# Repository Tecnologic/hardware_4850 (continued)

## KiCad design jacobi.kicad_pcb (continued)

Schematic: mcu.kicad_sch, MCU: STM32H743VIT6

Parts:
C601, C605, C608, C609, C610, C611, C612, C621, C622: 100n; C_0603_1608Metric; Part# CL10B104KBNC
C603, C620: 2u2; C_0603_1608Metric
C606, C607: 10u; C_1210_3225Metric; Part# CL32B106KLJNNNE
JP601: BTLDR; SolderJumper-2_P1.3mm_Open_RoundedPad1.0x1.5mm
R601: 11k; R_0603_1608Metric; Part# MCR03ERTJ113
R606, R607, R608, R609, R610, R611: 1R1; R_0603_1608Metric; Part# MCR03ERTJ1R1
R612: 10k; R_0603_1608Metric; Part# MCR03ERTJ103
U601: STM32H743VIT6; LQFP-100_14x14mm_P0.5mm; Part# 511-STM32H743VIT6; LCSC C114409
X601: Q33310F70051500; Oscillator_SMD_Abracon_ASE-4Pin_3.2x2.5mm; Part# Q33310F70051500; LCSC C32529

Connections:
+1V2: C603.1, C620.1, U601.48 (VCAP), U601.73 (VCAP)
+3.3VADC: C605.1, C606.1, C622.1, U601.20 (VREF+), U601.21 (VDDA); also elsewhere on the board
+3V3: C601.1, C607.1, C608.1, C609.1, C610.1, C611.1, C612.1, JP601.2 (B), R612.1, U601.6 (VBAT), U601.11 (VDD), U601.27 (VDD), U601.50 (VDD), U601.75 (VDD), U601.100 (VDD), X601.1 (EN), X601.4 (Vdd); also elsewhere on the board
/logic/controller/PWR_DET: R612.2, U601.3 (PE4); also elsewhere on the board
/logic/controller/PwmAH: R609.1; also elsewhere on the board
/logic/controller/PwmAL: R606.1; also elsewhere on the board
/logic/controller/PwmBH: R610.1; also elsewhere on the board
/logic/controller/PwmBL: R607.1; also elsewhere on the board
/logic/controller/PwmCH: R611.1; also elsewhere on the board
/logic/controller/PwmCL: R608.1; also elsewhere on the board
/logic/controller/analog/AIN_ACC: U601.15 (PC0); also elsewhere on the board
/logic/controller/analog/AIN_DCC: U601.32 (PC4); also elsewhere on the board
/logic/controller/analog/BrdgTemp: U601.23 (PA1); also elsewhere on the board
/logic/controller/analog/IaDC: U601.24 (PA2); also elsewhere on the board
/logic/controller/analog/IbDC: U601.25 (PA3); also elsewhere on the board
/logic/controller/analog/IcDC: U601.17 (PC2_C); also elsewhere on the board
/logic/controller/analog/MotTemp: U601.22 (PA0); also elsewhere on the board
/logic/controller/analog/V12PDC: U601.33 (PC5); also elsewhere on the board
/logic/controller/analog/VaDC: U601.35 (PB1); also elsewhere on the board
/logic/controller/analog/VbDC: U601.34 (PB0); also elsewhere on the board
/logic/controller/analog/VcDC: U601.18 (PC3_C); also elsewhere on the board
/logic/controller/interfaces/CAN_RXD: U601.81 (PD0); also elsewhere on the board
/logic/controller/interfaces/CAN_TXD: U601.82 (PD1); also elsewhere on the board
/logic/controller/interfaces/HallA: U601.59 (PD12); also elsewhere on the board
/logic/controller/interfaces/HallB: U601.60 (PD13); also elsewhere on the board
/logic/controller/interfaces/HallC: U601.61 (PD14); also elsewhere on the board
/logic/controller/interfaces/LED_ERROR: U601.98 (PE1); also elsewhere on the board
/logic/controller/interfaces/LED_MODE: U601.1 (PE2); also elsewhere on the board
/logic/controller/interfaces/LED_PWM: U601.2 (PE3); also elsewhere on the board
/logic/controller/interfaces/LED_RUN: U601.97 (PE0); also elsewhere on the board
/logic/controller/interfaces/PWM_EN: U601.45 (PE15); also elsewhere on the board
/logic/controller/interfaces/SWCLK: U601.76 (PA14); also elsewhere on the board
/logic/controller/interfaces/SWDIO: U601.72 (PA13); also elsewhere on the board
/logic/controller/interfaces/SWO: U601.89 (PB3); also elsewhere on the board
/logic/controller/mcu/AIN_VDC: U601.16 (PC1), U601.36 (PB2); also elsewhere on the board
/logic/controller/mcu/USB_DM: U601.70 (PA11); also elsewhere on the board
/logic/controller/mcu/USB_DP: U601.71 (PA12); also elsewhere on the board
/logic/controller/mcu/USB_VBUS: U601.4 (PE5); also elsewhere on the board
/logic/controller/mcu/\RESET: C621.1, U601.14 (NRST); also elsewhere on the board
GNDA: C605.2, C606.2, C622.2, U601.19 (VSSA); also elsewhere on the board
GNDD: C601.2, C603.2, C607.2, C608.2, C609.2, C610.2, C611.2, C612.2, C620.2, C621.2, R601.1, U601.10 (VSS), U601.26 (VSS), U601.49 (VSS), U601.74 (VSS), U601.99 (VSS), X601.2 (GND); also elsewhere on the board
unnamed: JP601.1 (A), R601.2, U601.94 (BOOT0)
unnamed: R609.2, U601.67 (PA8)
unnamed: R610.2, U601.68 (PA9)
unnamed: R611.2, U601.69 (PA10)
unnamed: R606.2, U601.52 (PB13)
unnamed: R607.2, U601.53 (PB14)
unnamed: R608.2, U601.54 (PB15)
unnamed: U601.12 (PH0), X601.3 (OUT)

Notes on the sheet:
STM32H743VIT6 core: supply decoupling, reset/boot/clock, PWM gate-drive series resistors

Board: 4 copper layers, 248 parts (15 on the bottom side), 157 nets, no tracks yet.

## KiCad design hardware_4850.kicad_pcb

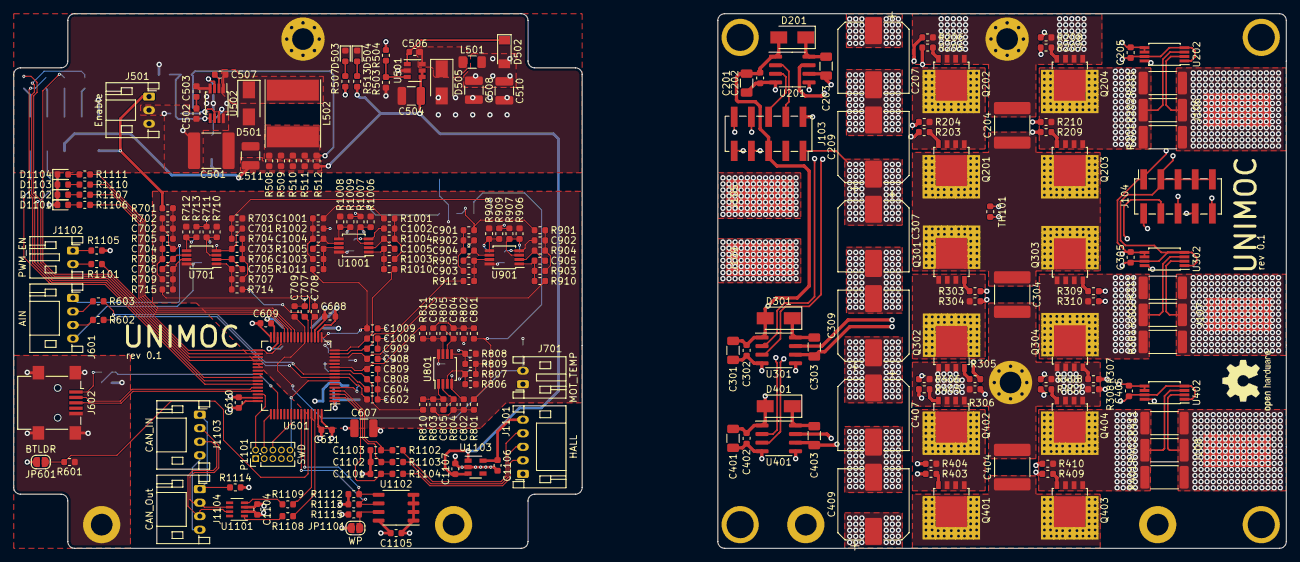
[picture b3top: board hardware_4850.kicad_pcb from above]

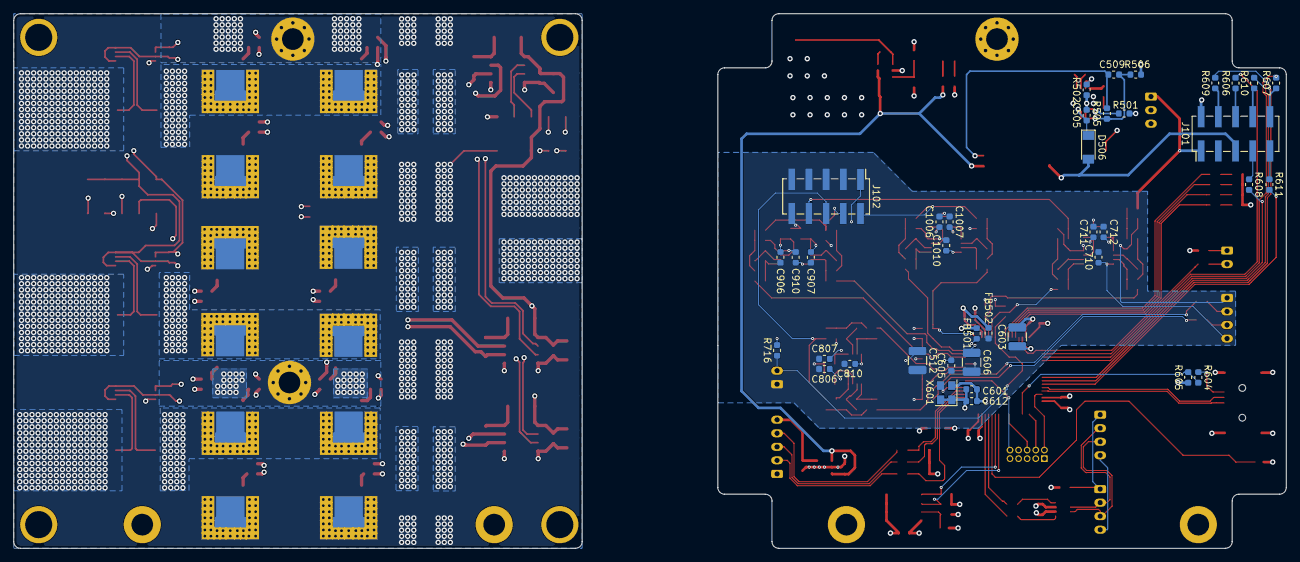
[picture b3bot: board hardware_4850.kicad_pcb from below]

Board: 4 copper layers, 188.1 x 79.0 mm, 290 parts (39 on the bottom side), 171 nets.

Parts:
C201, C203, C301, C303, C401, C403: 10u; C_1206_3216Metric
C202, C205, C302, C305, C402, C405, C502, C503, C506, C507, C601, C602, C604, C605, C608, C609, C610, C611, C612, C701, C707, C708, C709, C710, C711, C712, C806, C807, C808, C810, C906, C907, C908, C910, C1006, C1007, C1008, C1010, C1101, C1102, C1103, C1104, C1105: 100n; C_0603_1608Metric
C204, C304, C404, C501: 10u; C_2220_5650Metric
C207, C209, C307, C309, C407, C409: 56u; CP_Elec_10x10
C504, C508, C510, C511, C512: 22u; C_1210_3225Metric
C505, C1106, C1107: 1u; C_0603_1608Metric
C509: 2n2; C_0603_1608Metric
C603, C606, C607: 10u; C_1210_3225Metric
C702, C705, C706: 1n; C_0603_1608Metric
C703, C704: 10n; C_0603_1608Metric
C801, C802, C804, C901, C902, C904, C1001, C1002, C1004: 4n7; C_0603_1608Metric
C803, C805, C903, C905, C1003, C1005: 47p; C_0603_1608Metric
C809, C909, C1009: 100p; C_0603_1608Metric
D201, D301, D401, D501, D505: SS110R3G; D_SMA
D502, D506: PMLL4153; D_MiniMELF
D503: 3V3; LED_0603_1608Metric
D504: 12V; LED_0603_1608Metric
D1101: RUN; LED_0603_1608Metric
D1102: ERROR; LED_0603_1608Metric
D1103: FW; LED_0603_1608Metric
D1104: PWM; LED_0603_1608Metric
FB501, FB502: Ferrite_Bead_Small; R_0603_1608Metric
H101, H105, H106: GND; MountingHole_3.2mm_M3_Pad_Via
H102, H103, H104, H107: GND; MountingHole_3.2mm_M3_ISO14580_Pad
J101: PWM; PinHeader_2x05_P2.54mm_Vertical_SMD
J102: ADC; PinHeader_2x05_P2.54mm_Vertical_SMD
J103: PWM; PinSocket_2x05_P2.54mm_Vertical_SMD
J104: ADC; PinSocket_2x05_P2.54mm_Vertical_SMD
J105: +; SolderWirePad_1x01_SMD_5x10mm
J106: A; SolderWirePad_1x01_SMD_5x10mm
J107: B; SolderWirePad_1x01_SMD_5x10mm
J108: C; SolderWirePad_1x01_SMD_5x10mm
J109: GND; SolderWirePad_1x01_SMD_5x10mm
J501: Enable; JST_PH_S3B-PH-K_1x03_P2.00mm_Horizontal
J601: AIN; JST_PH_S4B-PH-K_1x04_P2.00mm_Horizontal
J602: USB_B_Mini; USB_Mini-B_Lumberg_2486_01_Horizontal
J701: MOT_TEMP; JST_PH_S2B-PH-K_1x02_P2.00mm_Horizontal
J1101: HALL; JST_PH_S5B-PH-K_1x05_P2.00mm_Horizontal
J1102: PWM_EN; JST_PH_S2B-PH-K_1x02_P2.00mm_Horizontal
J1103: CAN_IN; JST_PH_S4B-PH-K_1x04_P2.00mm_Horizontal
J1104: CAN_Out; JST_PH_S4B-PH-K_1x04_P2.00mm_Horizontal
JP601: BTLDR; SolderJumper-2_P1.3mm_Open_RoundedPad1.0x1.5mm
JP1101: WP; SolderJumper-2_P1.3mm_Open_RoundedPad1.0x1.5mm
L501: 4u7; L_1206_3216Metric
L502: 330u; L_Taiyo-Yuden_NR-80xx_HandSoldering
N101: Housing_Pad; RND-455-00370
P1101: SWD; PinHeader_2x05_P1.27mm_Vertical
Q201, Q202, Q203, Q204, Q301, Q302, Q303, Q304, Q401, Q402, Q403, Q404: NCEP6080AG; LFPAK56_ThermalVias-1
R201, R202, R211, R301, R302, R311, R401, R402, R411: 2mR; R_2512_6332Metric
R203, R204, R205, R206, R207, R208, R209, R210, R303, R304, R305, R306, R307, R308, R309, R310, R403, R404, R405, R406, R407, R408, R409, R410, R606, R607, R608, R609, R610, R611: 1R1; R_0603_1608Metric
R501: 220k; R_0603_1608Metric
R502: 100k; R_0603_1608Metric
R503, R505, R601, R602, R603, R605, R710, R711, R712, R713, R806, R807, R808, R809, R906, R907, R908, R909, R1006, R1007, R1008, R1009, R1115: 11k; R_0603_1608Metric
R504: 34k; R_0603_1608Metric
R506: 2k7; R_0603_1608Metric
R507, R1101, R1102, R1103, R1104, R1105, R1106, R1107, R1110, R1111: 510R; R_0603_1608Metric
R508, R509, R510, R511, R512, R1108, R1109, R1114: 11R; R_0603_1608Metric
R513: 3k3; R_0603_1608Metric
R604, R704, R705, R707, R709, R802, R902, R1002, R1112, R1113: 4k7; R_0603_1608Metric
R701: 24k 0.1%; R_0603_1608Metric
R702: 1k2 0.1%; R_0603_1608Metric
R703, R716: 10k 0.1%; R_0603_1608Metric
R706, R708: 47k; R_0603_1608Metric
R714, R715, R810, R811, R910, R911, R1010, R1011: 21R; R_0603_1608Metric
R801, R803, R901, R903, R1001, R1003: 9k1; R_0603_1608Metric
R804, R904, R1004: 470k; R_0603_1608Metric
R805, R905, R1005: 910k; R_0603_1608Metric
TH101: NTC 10k; R_0603_1608Metric
U201, U301, U401: LM5109BMA; SOIC-8_3.9x4.9mm_P1.27mm
U202, U302, U402: INA240A1PWR; TSSOP-8_4.4x3mm_P0.65mm
U501: LMR12010Y; SOT-23-6
U502: LM5008; MSOP-8_3x3mm_P0.65mm
U601: STM32F730R8Tx; LQFP-64_10x10mm_P0.5mm
U701, U801, U901, U1001: GS8632-MR; MSOP-8_3x3mm_P0.65mm
U1101: TCAN334; SOT-23-8
U1102: 24LC04; SO-8_3.9x4.9mm_P1.27mm
U1103: AP2204K-5.0; SOT-23-5
X601: SM44T; Oscillator_SMD_Abracon_ASE-4Pin_3.2x2.5mm

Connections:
+1V2: C603.1, U601.30
+3.3VA: C205.1, C305.1, C405.1, J104.1, U202.5, U202.6, U302.5, U302.6, U402.5, U402.6
+3.3VADC: C512.1, C605.1, C606.1, C710.1, C810.1, C910.1, C1010.1, FB501.1, J102.1, J601.4, R703.2, R710.2, R712.2, R716.2, R806.1, R808.1, R906.1, R908.1, R1006.1, R1008.1, U601.13, U701.8, U801.8, U901.8, U1001.8
+3V3: C508.1, C510.1, C601.1, C607.1, C608.1, C609.1, C610.1, C611.1, C612.1, C1104.1, C1105.1, D502.2, FB501.2, JP601.2, JP1101.1, L501.2, P1101.1, R504.2, R507.2, R1105.2, R1112.1, R1113.1, U601.1, U601.19, U601.32, U601.48, U601.64, U1101.3, U1102.8, X601.1, X601.4
+12P: C201.1, C202.1, C301.1, C302.1, C401.1, C402.1, D201.2, D301.2, D401.2, J103.5, U201.1, U301.1, U401.1
+12V: C504.1, C511.1, C1107.1, D506.2, J101.5, R508.1, R509.1, R510.1, R511.1, R512.1, R513.1, U501.4, U501.5, U1103.1, U1103.3
+48V: J101.1, J501.1, R701.2
+BATT: C204.1, C207.1, C209.1, C304.1, C307.1, C309.1, C404.1, C407.1, C409.1, J103.1, J105.1, Q201.5, Q203.5, Q301.5, Q303.5, Q401.5, Q403.5
/logic/controller/AIN_ACC: C602.1, R602.2, U601.8
/logic/controller/AIN_CUR_A: C808.2, R810.1, U601.10
/logic/controller/AIN_CUR_A_AC: C809.2, R811.1, U601.11
/logic/controller/AIN_DCC: C604.1, R603.2, U601.9
/logic/controller/BTLDR: JP601.1, R601.2, U601.60
/logic/controller/CAN_RX: R1109.2, U601.61
/logic/controller/CAN_TX: R1108.2, U601.62
/logic/controller/CLK: U601.5, X601.3
/logic/controller/EEPROM_SCL: R1113.2, U601.58, U1102.6
/logic/controller/EEPROM_SDA: R1112.2, U601.59, U1102.5
/logic/controller/Ia: C801.2, J102.6, R801.2
/logic/controller/Ib: C901.2, J102.4, R901.2
/logic/controller/Ic: C1001.2, J102.2, R1001.2
/logic/controller/PwmAH: J101.4, R609.1
/logic/controller/PwmAL: J101.6, R606.1
/logic/controller/PwmBH: J101.8, R610.1
/logic/controller/PwmBL: J101.10, R607.1
/logic/controller/PwmCH: J101.9, R611.1
/logic/controller/PwmCL: J101.7, R608.1
/logic/controller/TCK-SWCLK: P1101.4, U601.49
/logic/controller/TDO-SWO: P1101.6, U601.55
/logic/controller/TMS-SWDIO: P1101.2, U601.46
/logic/controller/Temp+: C701.1, J102.8, R703.1, R704.2
/logic/controller/USB_DM: J602.2, U601.44
/logic/controller/USB_DP: J602.3, U601.45
/logic/controller/USB_VBUS: R604.2, R605.2, U601.51
/logic/controller/\RESET: P1101.10, U601.7
/logic/controller/analog/BrdgTemp: C707.1, R714.2, U601.21
/logic/controller/analog/IbAC: C909.2, R911.1, U601.15
/logic/controller/analog/IbDC: C908.2, R910.1, U601.14
/logic/controller/analog/IcAC: C1009.2, R1011.1, U601.17
/logic/controller/analog/IcDC: C1008.2, R1010.1, U601.16
/logic/controller/analog/MotTemp: C709.1, J701.2, R716.1, U601.22
/logic/controller/analog/Vdc: C708.1, R715.2, U601.20
/logic/controller/interfaces/HallA: C1101.1, R1104.1, U601.2
/logic/controller/interfaces/HallB: C1102.1, R1103.1, U601.3
/logic/controller/interfaces/HallC: C1103.1, R1102.1, U601.4
/logic/controller/interfaces/LED_ERROR: R1107.2, U601.27
/logic/controller/interfaces/LED_MODE: R1110.2, U601.26
/logic/controller/interfaces/LED_PWM: R1111.2, U601.25
/logic/controller/interfaces/LED_RUN: R1106.2, U601.28
/logic/controller/interfaces/PWM_EN: R1101.2, U601.29, U601.33
/power/phase_a/I: J104.6, U202.8
/power/phase_a/Phase: J106.1, R201.1, R202.1, R211.1, U202.2
/power/phase_a/PwmH: J103.4, U201.2
/power/phase_a/PwmL: J103.6, U201.3
/power/phase_b/I: J104.4, U302.8
/power/phase_b/Phase: J107.1, R301.1, R302.1, R311.1, U302.2
/power/phase_b/PwmH: J103.8, U301.2
/power/phase_b/PwmL: J103.10, U301.3
/power/phase_c/I: J104.2, U402.8
/power/phase_c/Phase: J108.1, R401.1, R402.1, R411.1, U402.2
/power/phase_c/PwmH: J103.9, U401.2
/power/phase_c/PwmL: J103.7, U401.3
GND: C205.2, C305.2, C405.2, J104.3, J104.5, J104.7, J104.9, U202.1, U202.4, U202.7, U302.1, U302.4, U302.7, U402.1, U402.4, U402.7
GNDA: C512.2, C602.2, C604.2, C605.2, C606.2, C701.2, C702.1, C703.1, C704.1, C707.2, C708.2, C709.2, C710.2, C711.2, C712.2, C802.1, C806.1, C807.1, C808.1, C809.1, C810.2, C902.1, C906.1, C907.1, C908.1, C909.1, C910.2, C1002.1, C1006.1, C1007.1, C1008.1, C1009.1, C1010.2, FB502.1, J102.3, J102.5, J102.7, J102.9, J102.10, J601.1, J701.1, R702.2, R711.1, R713.1, R802.2, R807.2, R809.2, R902.2, R907.2, R909.2, R1002.2, R1007.2, R1009.2, U601.12, U701.4, U801.4, U901.4, U1001.4
GNDD: C501.2, C503.2, C504.2, C505.1, C508.2, C510.2, C511.2, C601.2, C603.2, C607.2, C608.2, C609.2, C610.2, C611.2, C612.2, C1101.2, C1102.2, C1103.2, C1104.2, C1105.2, C1106.2, C1107.2, D501.2, D503.1, D504.1, D505.2, D1101.1, D1102.1, D1103.1, D1104.1, FB502.2, H101.1, H102.1, H103.1, J101.2, J501.3, J602.5, J602.6, J1101.1, P1101.3, P1101.5, R502.1, R503.1, R506.1, R601.1, R605.1, R1114.2, R1115.2, U501.2, U502.4, U601.18, U601.31, U601.47, U601.63, U1101.2, U1102.1, U1102.2, U1102.3, U1102.4, U1103.2, X601.2
GNDPWR: C204.2, C207.2, C209.2, C304.2, C307.2, C309.2, C404.2, C407.2, C409.2, H104.1, H105.1, H106.1, H107.1, J103.2, J109.1, N101.1, Q202.1, Q202.2, Q202.3, Q204.1, Q204.2, Q204.3, Q302.1, Q302.2, Q302.3, Q304.1, Q304.2, Q304.3, Q402.1, Q402.2, Q402.3, Q404.1, Q404.2, Q404.3, R206.1, R208.1, R306.1, R308.1, R406.1, R408.1
unnamed: C502.2, C503.1
unnamed: C509.1, L502.2, R505.2, R508.2, R509.2, R510.2, R511.2, R512.2
unnamed: C702.2, R701.1, R702.1, R705.2
unnamed: C703.2, R704.1, R706.2, R707.2
unnamed: C704.2, R705.1, R708.2, R709.2
unnamed: C801.1, C803.2, C804.2, R802.1
unnamed: C802.2, R801.1, R803.2, R804.2
unnamed: C901.1, C903.2, C904.2, R902.1
unnamed: C902.2, R901.1, R903.2, R904.2
unnamed: C1001.1, C1003.2, C1004.2, R1002.1
unnamed: C1002.2, R1001.1, R1003.2, R1004.2
unnamed: C203.1, D201.1, U201.8
unnamed: C303.1, D301.1, U301.8
unnamed: C403.1, D401.1, U401.8
unnamed: C507.1, D501.1, L502.1, U502.1
unnamed: C506.2, D502.1, U501.1
unnamed: D503.2, R507.1
unnamed: D504.2, R513.2
unnamed: C506.1, D505.1, L501.1, U501.6
unnamed: C505.2, D506.1, U502.7
unnamed: D1101.2, R1106.1
unnamed: D1102.2, R1107.1
unnamed: D1103.2, R1110.1
unnamed: D1104.2, R1111.1
unnamed: J104.8, TH101.1
unnamed: J104.10, TH101.2
unnamed: C501.1, C502.1, J501.2, R501.2, U502.8
unnamed: J601.2, R603.1
unnamed: J601.3, R602.1
unnamed: J602.1, R604.1
unnamed: J1101.2, R1104.2
unnamed: J1101.3, R1103.2
unnamed: J1101.4, R1102.2
unnamed: C1106.1, J1101.5, U1103.5
unnamed: J1102.1, R1105.1
unnamed: J1102.2, R1101.1
unnamed: J1103.1, J1104.1, R1114.1
unnamed: J1103.2, J1104.2, U1101.6
unnamed: J1103.3, J1104.3, U1101.7
unnamed: J1103.4, J1104.4
unnamed: JP1101.2, R1115.1, U1102.7
unnamed: Q201.4, R203.1
unnamed: Q201.1, Q201.2, Q201.3, Q202.5, Q203.1, Q203.2, Q203.3, Q204.5, R201.2, R202.2, R204.1, R210.1, R211.2, U202.3
unnamed: Q202.4, R205.1
unnamed: Q203.4, R209.1
unnamed: Q204.4, R207.1
unnamed: Q301.4, R303.1
unnamed: Q301.1, Q301.2, Q301.3, Q302.5, Q303.1, Q303.2, Q303.3, Q304.5, R301.2, R302.2, R304.1, R310.1, R311.2, U302.3
unnamed: Q302.4, R305.1
unnamed: Q303.4, R309.1
unnamed: Q304.4, R307.1
unnamed: Q401.4, R403.1
unnamed: Q401.1, Q401.2, Q401.3, Q402.5, Q403.1, Q403.2, Q403.3, Q404.5, R401.2, R402.2, R404.1, R410.1, R411.2, U402.3
unnamed: Q402.4, R405.1
unnamed: Q403.4, R409.1
unnamed: Q404.4, R407.1
unnamed: R203.2, R209.2, U201.7
unnamed: C203.2, R204.2, R210.2, U201.6
unnamed: R205.2, R207.2, U201.5
unnamed: C201.2, C202.2, R206.2, R208.2, U201.4
unnamed: R303.2, R309.2, U301.7
unnamed: C303.2, R304.2, R310.2, U301.6
unnamed: R305.2, R307.2, U301.5
unnamed: C301.2, C302.2, R306.2, R308.2, U301.4
unnamed: R403.2, R409.2, U401.7
unnamed: C403.2, R404.2, R410.2, U401.6
unnamed: R405.2, R407.2, U401.5
unnamed: C401.2, C402.2, R406.2, R408.2, U401.4
unnamed: R503.2, R504.1, U501.3
unnamed: C507.2, U502.2
unnamed: C509.2, R505.1, R506.2, U502.5
unnamed: R502.2, U502.3
unnamed: R501.1, U502.6
unnamed: R609.2, U601.41
unnamed: R610.2, U601.42
unnamed: R611.2, U601.43
unnamed: R606.2, U601.34
unnamed: R607.2, U601.35
unnamed: R608.2, U601.36
unnamed: C711.1, R710.1, R711.2, U701.3
unnamed: C705.2, R706.1, U701.2
unnamed: C705.1, R707.1, R714.1, U701.1
unnamed: C712.1, R712.1, R713.2, U701.5
unnamed: C706.2, R708.1, U701.6
unnamed: C706.1, R709.1, R715.1, U701.7
unnamed: C806.2, R806.2, R807.1, U801.3
unnamed: C805.1, R804.1, U801.2
unnamed: C805.2, R803.1, R810.2, U801.1
unnamed: C807.2, R808.2, R809.1, U801.5
unnamed: C804.1, R805.2, U801.6
unnamed: C803.1, R805.1, R811.2, U801.7
unnamed: C906.2, R906.2, R907.1, U901.3
unnamed: C905.1, R904.1, U901.2
unnamed: C905.2, R903.1, R910.2, U901.1
unnamed: C907.2, R908.2, R909.1, U901.5
unnamed: C904.1, R905.2, U901.6
unnamed: C903.1, R905.1, R911.2, U901.7
unnamed: C1006.2, R1006.2, R1007.1, U1001.3
unnamed: C1005.1, R1004.1, U1001.2
unnamed: C1005.2, R1003.1, R1010.2, U1001.1
unnamed: C1007.2, R1008.2, R1009.1, U1001.5
unnamed: C1004.1, R1005.2, U1001.6
unnamed: C1003.1, R1005.1, R1011.2, U1001.7
unnamed: R1109.1, U1101.4
unnamed: R1108.1, U1101.1

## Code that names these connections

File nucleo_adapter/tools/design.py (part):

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], [
    dict(ref='J101', lib='Connector_Generic:Conn_02x05_Odd_Even', value='PWM',
         fp='Connector_PinHeader_2.54mm:PinHeader_2x05_P2.54mm_Vertical_SMD',
         pins={'1': '+BATT', '2': 'GND', '3': NC, '4': 'PWM_AH', '5': '+12V',
               '6': 'PWM_AL', '7': 'PWM_CL', '8': 'PWM_BH', '9': 'PWM_CH', '10': 'PWM_BL'}),
    dict(ref='J102', lib='Connector_Generic:Conn_02x05_Odd_Even', value='ADC',
         fp='Connector_PinHeader_2.54mm:PinHeader_2x05_P2.54mm_Vertical_SMD',
         pins={'1': '+3.3VA', '2': 'I_C', '3': 'GNDA', '4': 'I_B', '5': 'GNDA',
               '6': 'I_A', '7': 'GNDA', '8': 'T_BRIDGE', '9': 'GNDA', '10': 'GNDA'}),
    dict(ref='H101', lib='Mechanical:MountingHole_Pad', value='M3',
         fp='MountingHole:MountingHole_3.2mm_M3_Pad_Via', pins={'1': 'GND'}),
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
# ---------------------------------------------------------------- nucleo
NUCLEO_MAP = {
    'PE9': 'TIM1_CH1', 'PE8': 'TIM1_CH1N', 'PE11': 'TIM1_CH2', 'PE10': 'TIM1_CH2N',
    'PE13': 'TIM1_CH3', 'PE12': 'TIM1_CH3N', 'PE15': 'TIM1_BKIN',
    'PA6': 'ADC_IA', 'PB1': 'ADC_IB', 'PC2': 'ADC_IC', 'PC3': 'ADC_VDC',
    'PF11': 'ADC_VA', 'PF13': 'ADC_VB', 'PF10': 'ADC_VC',
    'PF12': 'ADC_TBRIDGE', 'PF14': 'ADC_TMOTOR',
    'PD12': 'HALL_A', 'PD13': 'HALL_B', 'PD14': 'HALL_C',
    'PD0': 'CAN_RX', 'PD1': 'CAN_TX',
    '+3V3': '+3V3', '+5V': '+5V', 'GND': 'GND', 'AGND': 'GND',
}
sheet('nucleo', 'NUCLEO-H743ZI', [
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    'Plugs into two 2 x 36 morpho sockets (CN11, CN12)',
    'on the top side. Pin map: unimoc',
    'app/boards/nucleo_h743zi.overlay (hardware/first-startup).',
    'PC2/PC3 are PC2_C/PC3_C on the H743 (ADC3 direct pads).',
    'Powered from the ST-LINK USB. Its +3V3 (= VDDA, the ADC',
    'reference) also feeds +3.3VA through FB601 (sheet supply).',
    'AGND is GND on the Nucleo, so it goes to GND here;',
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    C('C304', '100n', 'ADC_TBRIDGE', 'GNDA'),
    dict(ref='J301', lib='Connector_Generic:Conn_01x02', value='MOT_TEMP',
         fp='Connector_JST:JST_PH_B2B-PH-K_1x02_P2.00mm_Vertical',
         pins={'1': 'T_MOTOR', '2': 'GNDA'}),
    R('R306', '10k', '+3.3VA', 'T_MOTOR'),
    R('R307', '1k', 'T_MOTOR', 'ADC_TMOTOR'),
    C('C305', '100n', 'ADC_TMOTOR', 'GNDA'),
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    C('C306', '1n', 'ADC_VDC', 'GNDA'),
    dict(br=True, ref='J302', lib='Connector_Generic:Conn_01x03', value='VPHASE',
         fp='Connector_JST:JST_PH_B3B-PH-K_1x03_P2.00mm_Vertical',
         pins={'1': 'V_A', '2': 'V_B', '3': 'V_C'}),
]
for k, ph in enumerate('ABC'):
    vs += [R(f'R3{10 + 2 * k}', '47k 0.1%', f'V_{ph}', f'ADC_V{ph}', br=(k == 0)),
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gate += [
    dict(br=True, ref='J401', lib='Connector_Generic:Conn_01x02', value='ENABLE',
         fp='Connector_JST:JST_PH_B2B-PH-K_1x02_P2.00mm_Vertical',
         pins={'1': 'EN_SUPPLY', '2': 'EN_IN'}),
    R('R421', '1k', '+3V3', 'EN_SUPPLY'),
    R('R422', '10k', 'EN_IN', 'GND'),
    R('R423', '1k', 'EN_IN', 'TIM1_BKIN'),
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    'TIM1 CH1..CH3 / CH1N..CH3N drive the LM5109B inputs HI/LI on the power board (TTL',
    'thresholds, 3.3 V logic is enough: check VIH in the datasheet). 100R series near the',
    'Nucleo, 10k pull-down near J101: the gates stay off while the MCU is in reset.',
    'ENABLE (J401): close the loop (switch or E-stop) to release TIM1_BKIN (PE15, active low).',
    'Open loop = break, all six outputs off. Matches the firmware (pull-down on PE15).',
], gate)

# ---------------------------------------------------------------- interfaces
itf = [
    dict(ref='U501', lib='Interface_CAN_LIN:TCAN334', value='TCAN334D',
         fp='Package_SO:SOIC-8_3.9x4.9mm_P1.27mm',
         pins={'1': 'CAN_TX', '2': 'GND', '3': '+3V3', '4': 'CAN_RX', '5': 'CAN_SHDN',
               '6': 'CAN_L', '7': 'CAN_H', '8': 'CAN_STB'}),
    C('C501', '100n', '+3V3', 'GND'),
    R('R501', '10k', 'CAN_SHDN', 'GND'),
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    R('R503', '120R', 'CAN_H', 'CAN_TERM'),
    dict(ref='JP501', lib='Jumper:SolderJumper_2_Open', value='TERM',
         fp='Jumper:SolderJumper-2_P1.3mm_Open_RoundedPad1.0x1.5mm',
         pins={'1': 'CAN_TERM', '2': 'CAN_L'}),
]
for k in range(2):
    itf.append(dict(ref=f'J50{k + 1}', lib='Connector_Generic_MountingPin:Conn_01x04_MountingPin',
                    value='CAN', fp='Connector_JST:JST_GH_SM04B-GHS-TB_1x04-1MP_P1.25mm_Horizontal',
                    pins={'1': NC, '2': 'CAN_H', '3': 'CAN_L', '4': 'GND', 'MP': 'GND'}))
itf.append(dict(br=True, ref='J503', lib='Connector_Generic:Conn_01x05', value='HALL',
                fp='Connector_JST:JST_PH_B5B-PH-K_1x05_P2.00mm_Vertical',
                pins={'1': '+5V', '2': 'HALL_A_IN', '3': 'HALL_B_IN', '4': 'HALL_C_IN', '5': 'GND'}))
itf.append(dict(ref='#FLG501', lib='power:PWR_FLAG', value='PWR_FLAG', fp='', pins={'1': '+5V'}))
for k, h in enumerate('ABC'):
    itf += [R(f'R5{11 + k}', '2k2', '+3V3', f'HALL_{h}_IN', br=(k == 0)),
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            C(f'C5{11 + k}', '1n', f'HALL_{h}', 'GND')]
sheet('interfaces', 'CAN FD and Hall sensors', [
    'CAN FD and Hall sensors',
    'TCAN334 (CAN FD, 3.3 V) on FDCAN1 (PD0 RX, PD1 TX). SHDN and STB pulled low: always on.',
    'J501/J502: Cyphal/UAVCAN micro connector (JST GH 4): 1 +5V (not connected here),',
    '2 CAN_H, 3 CAN_L, 4 GND. Close JP501 for the 120R termination at a bus end.',
    'HALL (J503, JST PH 5): open-collector sensors on +5V, 2k2 pull-ups to +3V3, 1k / 1n RC.',
    'PD12..PD14 are 5 V tolerant.',
], itf)

# ---------------------------------------------------------------- supply
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    C('C602', '100n', '+12V', 'GND'),
    R('R601', '4k7', '+12V', 'LED_12V'),
    dict(ref='D603', lib='Device:LED', value='green', fp='LED_SMD:LED_0603_1608Metric',
         pins={'1': 'GND', '2': 'LED_12V'}, rot=90),
    dict(br=True, ref='FB601', lib='Device:FerriteBead_Small', value='BLM18PG221', fp=FB0603,
         pins={'1': '+3V3', '2': '+3.3VA'}),
    C('C603', '10u', '+3.3VA', 'GNDA'),
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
